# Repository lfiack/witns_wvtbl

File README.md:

# witns_wvtbl
Wavetable oscillator

## Make the project work
This project uses a submodule for the KiCAD library. To get it properly, use the `--recursive` option when cloning the repo :
```
git clone --recursive git@github.com:lfiack/witns_wvtbl.git
```

The firmware is developped with VSCode and the `stm32-for-vscode` plugin. There is now a plugin developped by ST, but I didn't take time to test it.

## Where to download wavetables ?
* [Free Serum Wavetables](https://www.antidoteaudio.com/free-serum-wavetables)
* [Adventurekid](https://www.adventurekid.se/akrt/waveforms/)

## TODO
* Add -12V Label

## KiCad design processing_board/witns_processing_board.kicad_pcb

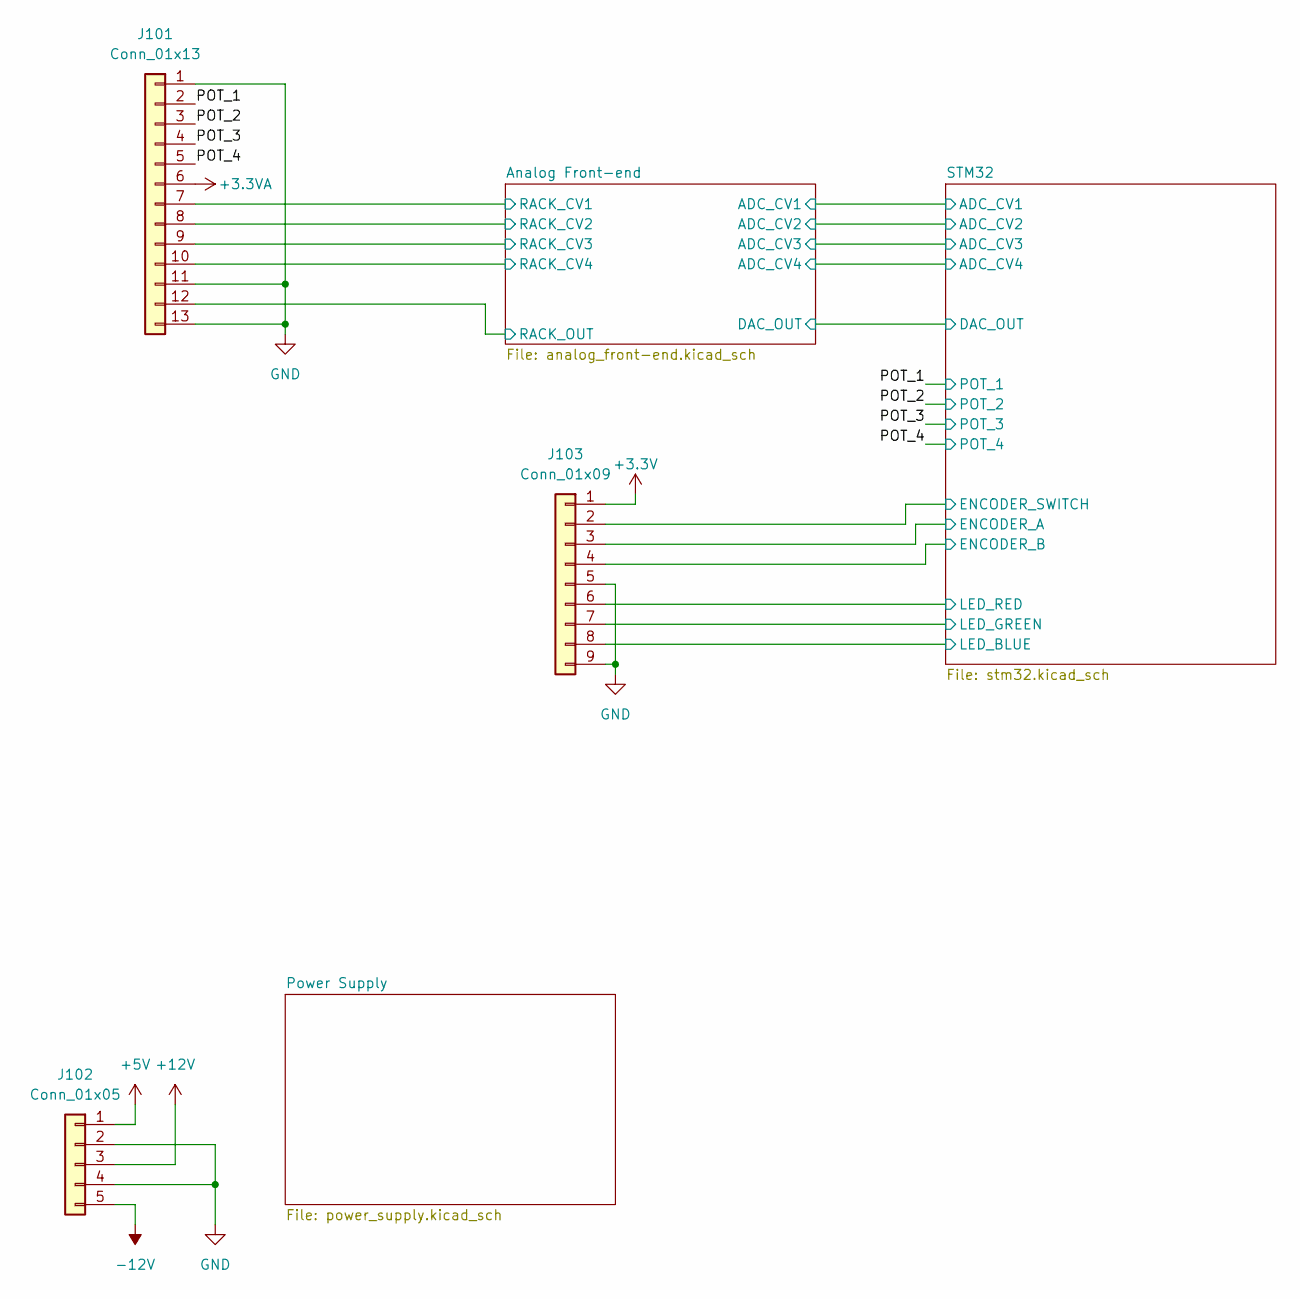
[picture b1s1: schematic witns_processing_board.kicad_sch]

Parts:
J101: Conn_01x13; PinHeader_1x13_P2.54mm_Vertical
J102: Conn_01x05; PinHeader_1x05_P2.54mm_Vertical
J103: Conn_01x09; PinHeader_1x09_P2.54mm_Vertical

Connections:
+3.3VA: J101.6; also elsewhere on the board
+3V3: J103.1; also elsewhere on the board
+5V: J102.1; also elsewhere on the board
+12V: J102.3; also elsewhere on the board
-12V: J102.5; also elsewhere on the board
/Analog Front-end/RACK_CV1: J101.7; also elsewhere on the board
/Analog Front-end/RACK_CV2: J101.8; also elsewhere on the board
/Analog Front-end/RACK_CV3: J101.9; also elsewhere on the board
/Analog Front-end/RACK_CV4: J101.10; also elsewhere on the board
/Analog Front-end/RACK_OUT: J101.12; also elsewhere on the board
/POT_1: J101.2; also elsewhere on the board
/POT_2: J101.3; also elsewhere on the board
/POT_3: J101.4; also elsewhere on the board
/POT_4: J101.5; also elsewhere on the board
/STM32/ENCODER_A: J103.3; also elsewhere on the board
/STM32/ENCODER_B: J103.4; also elsewhere on the board
/STM32/ENCODER_SWITCH: J103.2; also elsewhere on the board
/STM32/LED_BLUE: J103.8; also elsewhere on the board
/STM32/LED_GREEN: J103.7; also elsewhere on the board
/STM32/LED_RED: J103.6; also elsewhere on the board
GND: J101.1, J101.11, J101.13, J102.2, J102.4, J103.5, J103.9; also elsewhere on the board

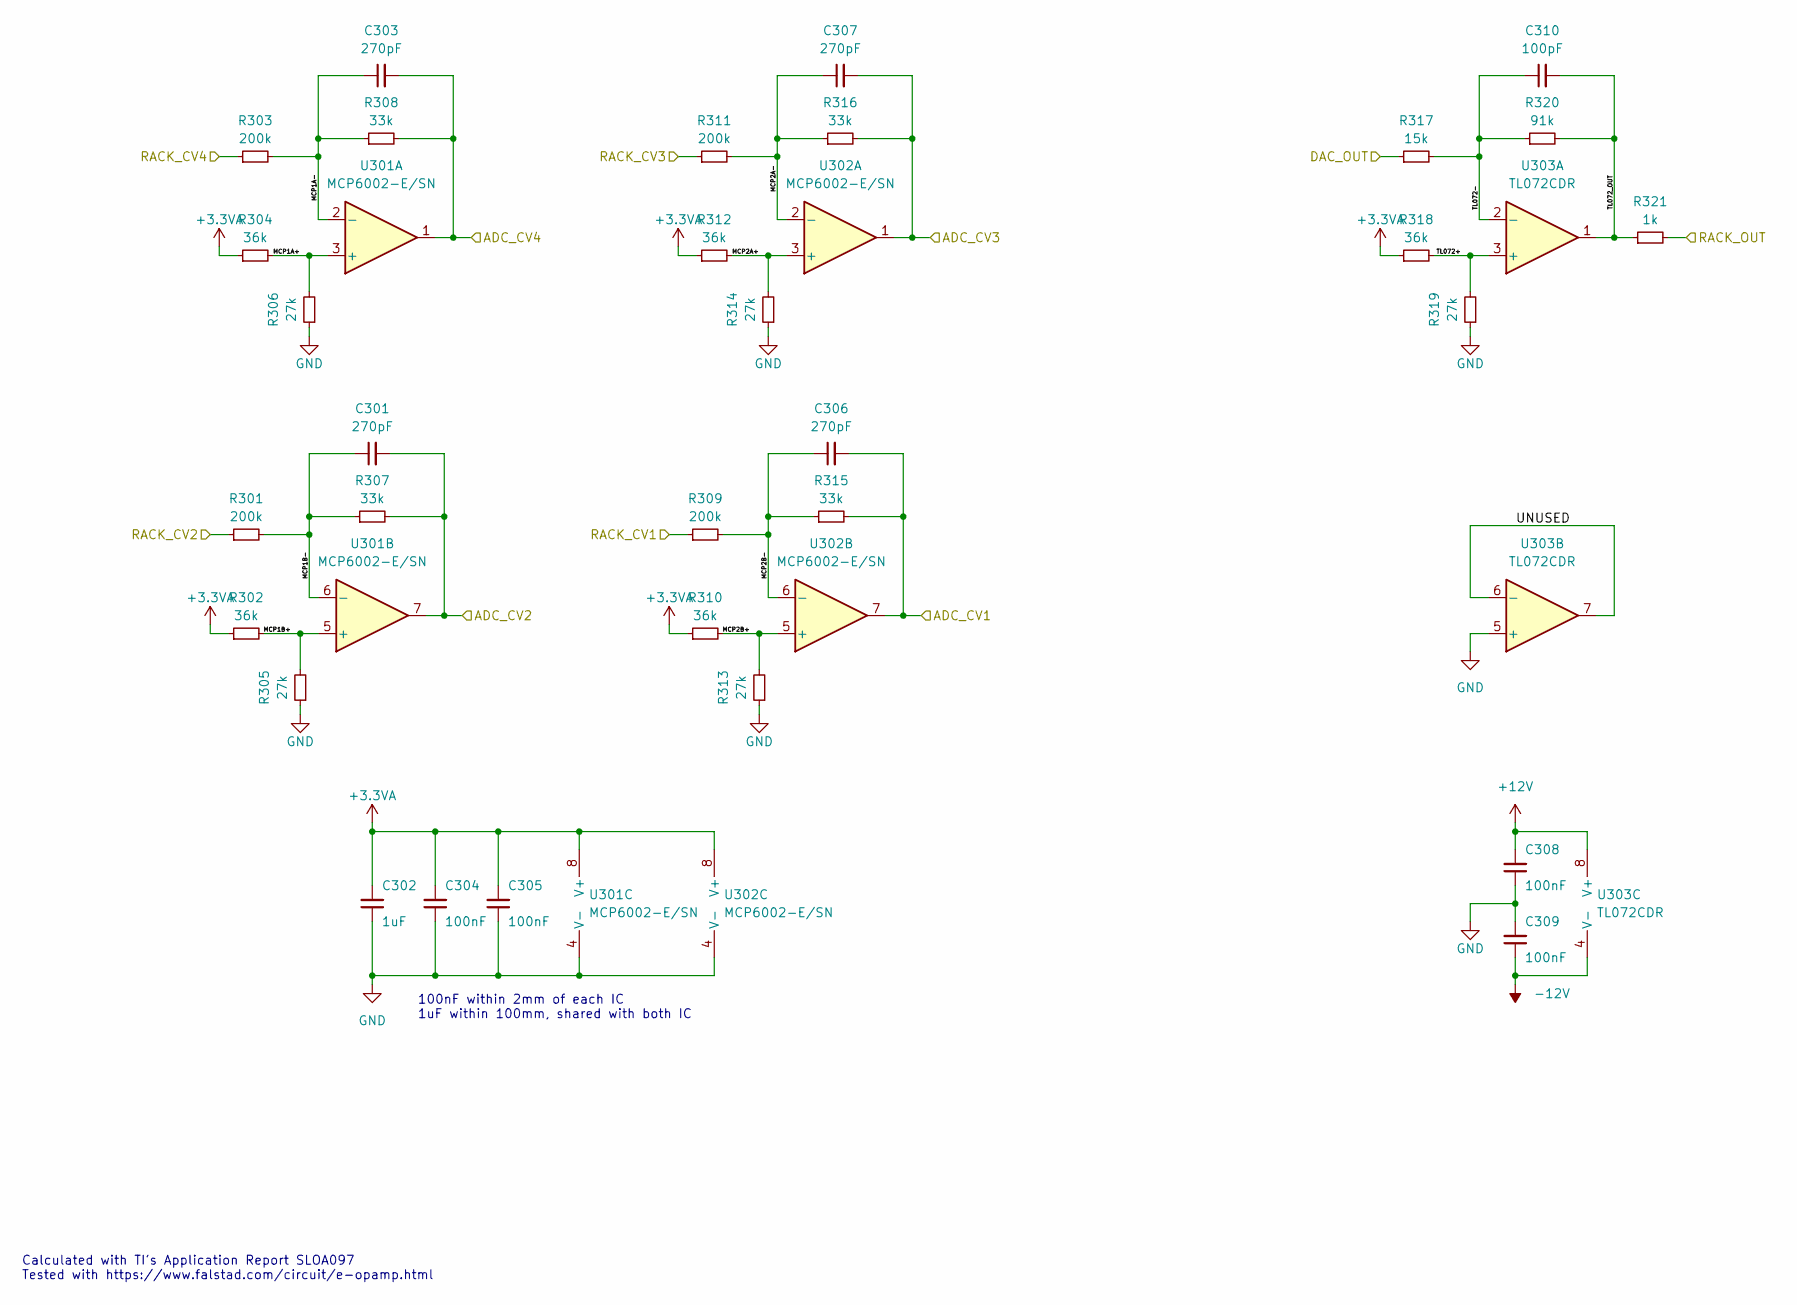
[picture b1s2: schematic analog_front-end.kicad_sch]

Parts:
C301, C303, C306, C307: 270pF; C_0603_1608Metric
C302: 1uF; C_0603_1608Metric
C304, C305, C308, C309: 100nF; C_0603_1608Metric
C310: 100pF; C_0603_1608Metric
R301, R303, R309, R311: 200k; R_0603_1608Metric
R302, R304, R310, R312, R318: 36k; R_0603_1608Metric
R305, R306, R313, R314, R319: 27k; R_0603_1608Metric
R307, R308, R315, R316: 33k; R_0603_1608Metric
R317: 15k; R_0603_1608Metric
R320: 91k; R_0603_1608Metric
R321: 1k; R_0603_1608Metric
U301, U302: MCP6002-E/SN; SOIC-8_3.9x4.9mm_P1.27mm
U303: TL072CDR; SOIC-8_3.9x4.9mm_P1.27mm

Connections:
+3.3VA: C302.2, C304.2, C305.2, R302.1, R304.1, R310.1, R312.1, R318.1, U301.8 (V+), U302.8 (V+); also elsewhere on the board
+12V: C308.2, U303.8 (V+); also elsewhere on the board
-12V: C309.1, U303.4 (V-); also elsewhere on the board
/Analog Front-end/ADC_CV1: C306.2, R315.2, U302.7; also elsewhere on the board
/Analog Front-end/ADC_CV2: C301.2, R307.2, U301.7; also elsewhere on the board
/Analog Front-end/ADC_CV3: C307.2, R316.2, U302.1; also elsewhere on the board
/Analog Front-end/ADC_CV4: C303.2, R308.2, U301.1; also elsewhere on the board
/Analog Front-end/DAC_OUT: R317.1; also elsewhere on the board
/Analog Front-end/MCP1A+: R304.2, R306.2, U301.3 (+)
/Analog Front-end/MCP1A-: C303.1, R303.2, R308.1, U301.2 (-)
/Analog Front-end/MCP1B+: R302.2, R305.2, U301.5 (+)
/Analog Front-end/MCP1B-: C301.1, R301.2, R307.1, U301.6 (-)
/Analog Front-end/MCP2A+: R312.2, R314.2, U302.3 (+)
/Analog Front-end/MCP2A-: C307.1, R311.2, R316.1, U302.2 (-)
/Analog Front-end/MCP2B+: R310.2, R313.2, U302.5 (+)
/Analog Front-end/MCP2B-: C306.1, R309.2, R315.1, U302.6 (-)
/Analog Front-end/RACK_CV1: R309.1; also elsewhere on the board
/Analog Front-end/RACK_CV2: R301.1; also elsewhere on the board
/Analog Front-end/RACK_CV3: R311.1; also elsewhere on the board
/Analog Front-end/RACK_CV4: R303.1; also elsewhere on the board
/Analog Front-end/RACK_OUT: R321.2; also elsewhere on the board
/Analog Front-end/TL072+: R318.2, R319.2, U303.3 (+)
/Analog Front-end/TL072-: C310.1, R317.2, R320.1, U303.2 (-)
/Analog Front-end/TL072_OUT: C310.2, R320.2, R321.1, U303.1
/Analog Front-end/UNUSED: U303.6 (-), U303.7
GND: C302.1, C304.1, C305.1, C308.1, C309.2, R305.1, R306.1, R313.1, R314.1, R319.1, U301.4 (V-), U302.4 (V-), U303.5 (+); also elsewhere on the board

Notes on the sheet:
100nF within 2mm of each IC 1uF within 100mm, shared with both IC
Calculated with TI's Application Report SLOA097 Tested with https://www.falstad.com/circuit/e-opamp.html

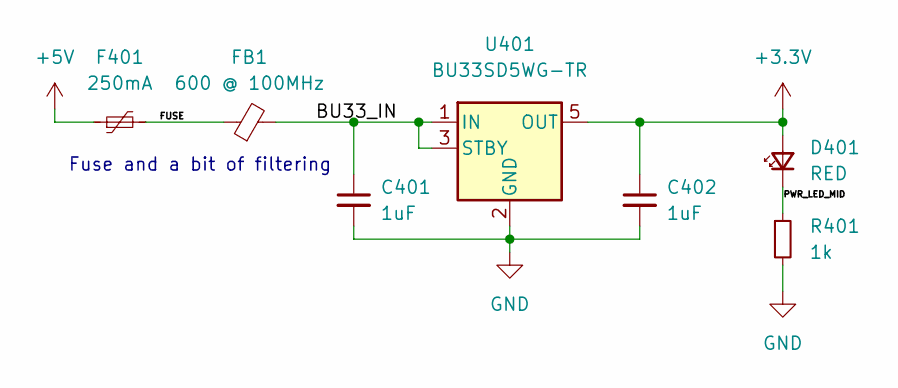
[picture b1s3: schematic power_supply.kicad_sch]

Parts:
C401, C402: 1uF; C_0603_1608Metric_Pad1.08x0.95mm_HandSolder
D401: RED; LED_0603_1608Metric_Pad1.05x0.95mm_HandSolder
F401: 250mA; Fuse_1206_3216Metric_Pad1.42x1.75mm_HandSolder; Farnell 2834880
FB1: 600 @ 100MHz; L_0805_2012Metric_Pad1.15x1.40mm_HandSolder; Farnell 2292460
R401: 1k; R_0603_1608Metric_Pad0.98x0.95mm_HandSolder
U401: BU33SD5WG-TR; SOT-23-5

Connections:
+3V3: C402.1, D401.2 (A), U401.5 (OUT); also elsewhere on the board
+5V: F401.1; also elsewhere on the board
/Power Supply/BU33_IN: C401.1, FB1.2, U401.1 (IN), U401.3 (STBY)
/Power Supply/FUSE: F401.2, FB1.1
/Power Supply/PWR_LED_MID: D401.1 (K), R401.1
GND: C401.2, C402.2, R401.2, U401.2 (GND); also elsewhere on the board

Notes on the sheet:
Fuse and a bit of filtering

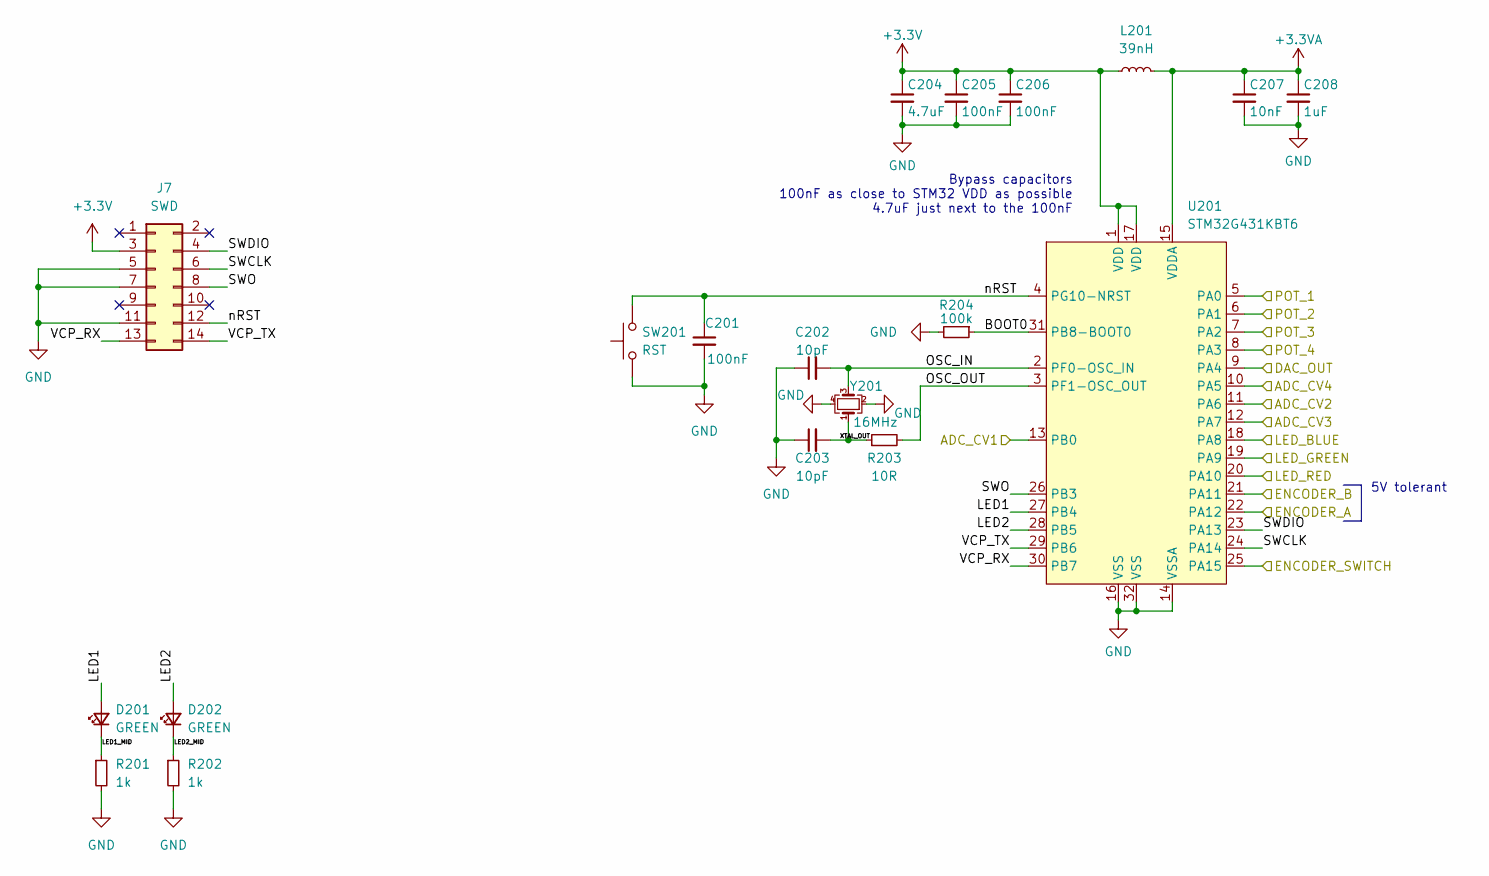
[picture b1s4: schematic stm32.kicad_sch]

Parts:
C201: 100nF; C_0603_1608Metric
C202, C203: 10pF; C_0603_1608Metric
C204: 4.7uF; C_0603_1608Metric_Pad1.08x0.95mm_HandSolder; Farnell 3013398
C205, C206: 100nF; C_0603_1608Metric_Pad1.08x0.95mm_HandSolder
C207: 10nF; C_0603_1608Metric_Pad1.08x0.95mm_HandSolder
C208: 1uF; C_0603_1608Metric_Pad1.08x0.95mm_HandSolder; Farnell 3013398
D201, D202: GREEN; LED_0603_1608Metric
J7: Conn_02x07_Odd_Even; PinHeader_2x07_P1.27mm_Vertical_SMD; Farnell 3226055
L201: 39nH; L_0603_1608Metric
R201, R202: 1k; R_0603_1608Metric
R203: 10R; R_0603_1608Metric
R204: 100k; R_0603_1608Metric
SW201: RST; SW_SPST_B3U-1000P; Farnell 1333652
U201: STM32G431KBT6; LQFP-32_7x7mm_P0.8mm
Y201: 16MHz; Crystal_SMD_EuroQuartz_MT-4Pin_3.2x2.5mm; Farnell 2853935

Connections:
+3.3VA: C207.1, C208.1, L201.2, U201.15 (VDDA); also elsewhere on the board
+3V3: C204.1, C205.1, C206.1, J7.3, L201.1, U201.1 (VDD), U201.17 (VDD); also elsewhere on the board
/Analog Front-end/ADC_CV1: U201.13 (PB0); also elsewhere on the board
/Analog Front-end/ADC_CV2: U201.11 (PA6); also elsewhere on the board
/Analog Front-end/ADC_CV3: U201.12 (PA7); also elsewhere on the board
/Analog Front-end/ADC_CV4: U201.10 (PA5); also elsewhere on the board
/Analog Front-end/DAC_OUT: U201.9 (PA4); also elsewhere on the board
/POT_1: U201.5 (PA0); also elsewhere on the board
/POT_2: U201.6 (PA1); also elsewhere on the board
/POT_3: U201.7 (PA2); also elsewhere on the board
/POT_4: U201.8 (PA3); also elsewhere on the board
/STM32/BOOT0: R204.1, U201.31 (PB8-BOOT0)
/STM32/ENCODER_A: U201.22 (PA12); also elsewhere on the board
/STM32/ENCODER_B: U201.21 (PA11); also elsewhere on the board
/STM32/ENCODER_SWITCH: U201.25 (PA15); also elsewhere on the board
/STM32/LED1: D201.2 (A), U201.27 (PB4)
/STM32/LED1_MID: D201.1 (K), R201.1
/STM32/LED2: D202.2 (A), U201.28 (PB5)
/STM32/LED2_MID: D202.1 (K), R202.1
/STM32/LED_BLUE: U201.18 (PA8); also elsewhere on the board
/STM32/LED_GREEN: U201.19 (PA9); also elsewhere on the board
/STM32/LED_RED: U201.20 (PA10); also elsewhere on the board
/STM32/OSC_IN: C202.2, U201.2 (PF0-OSC_IN), Y201.3
/STM32/OSC_OUT: R203.2, U201.3 (PF1-OSC_OUT)
/STM32/SWCLK: J7.6, U201.24 (PA14)
/STM32/SWDIO: J7.4, U201.23 (PA13)
/STM32/SWO: J7.8, U201.26 (PB3)
/STM32/VCP_RX: J7.13, U201.30 (PB7)
/STM32/VCP_TX: J7.14, U201.29 (PB6)
/STM32/XTAL_OUT: C203.2, R203.1, Y201.1
/STM32/nRST: C201.1, J7.12, SW201.2, U201.4 (PG10-NRST)
GND: C201.2, C202.1, C203.1, C204.2, C205.2, C206.2, C207.2, C208.2, J7.5, J7.7, J7.11, R201.2, R202.2, R204.2, SW201.1, U201.14 (VSSA), U201.16 (VSS), U201.32 (VSS), Y201.2, Y201.4; also elsewhere on the board

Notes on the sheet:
5V tolerant
Bypass capacitors 100nF as close to STM32 VDD as possible 4.7uF just next to the 100nF

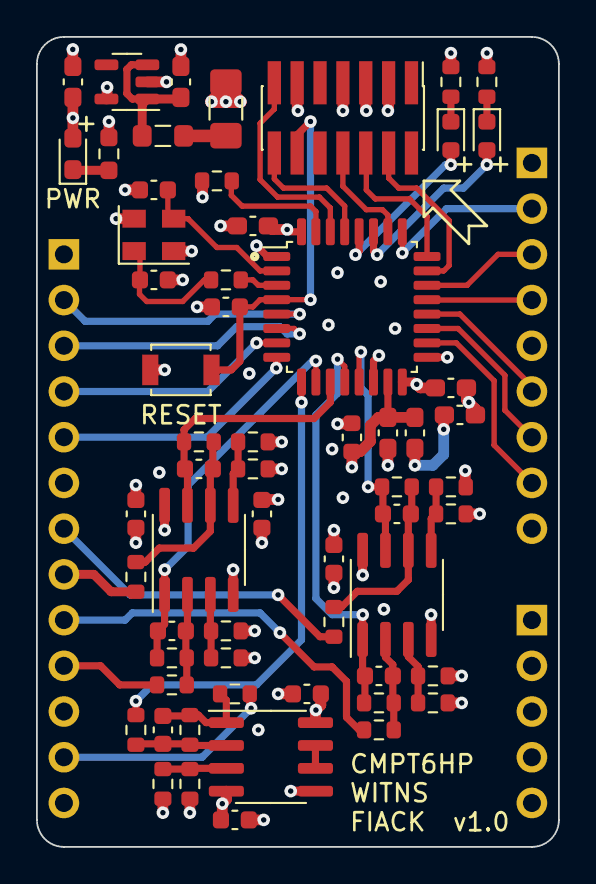
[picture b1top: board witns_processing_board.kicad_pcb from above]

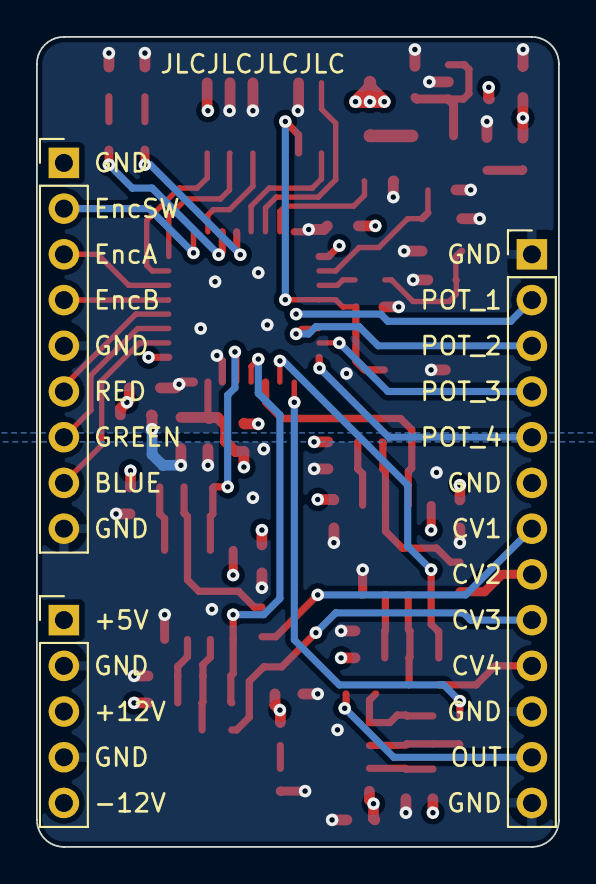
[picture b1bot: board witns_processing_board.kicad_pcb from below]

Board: 4 copper layers, 29.0 x 45.0 mm, 63 parts (3 on the bottom side), 55 nets.

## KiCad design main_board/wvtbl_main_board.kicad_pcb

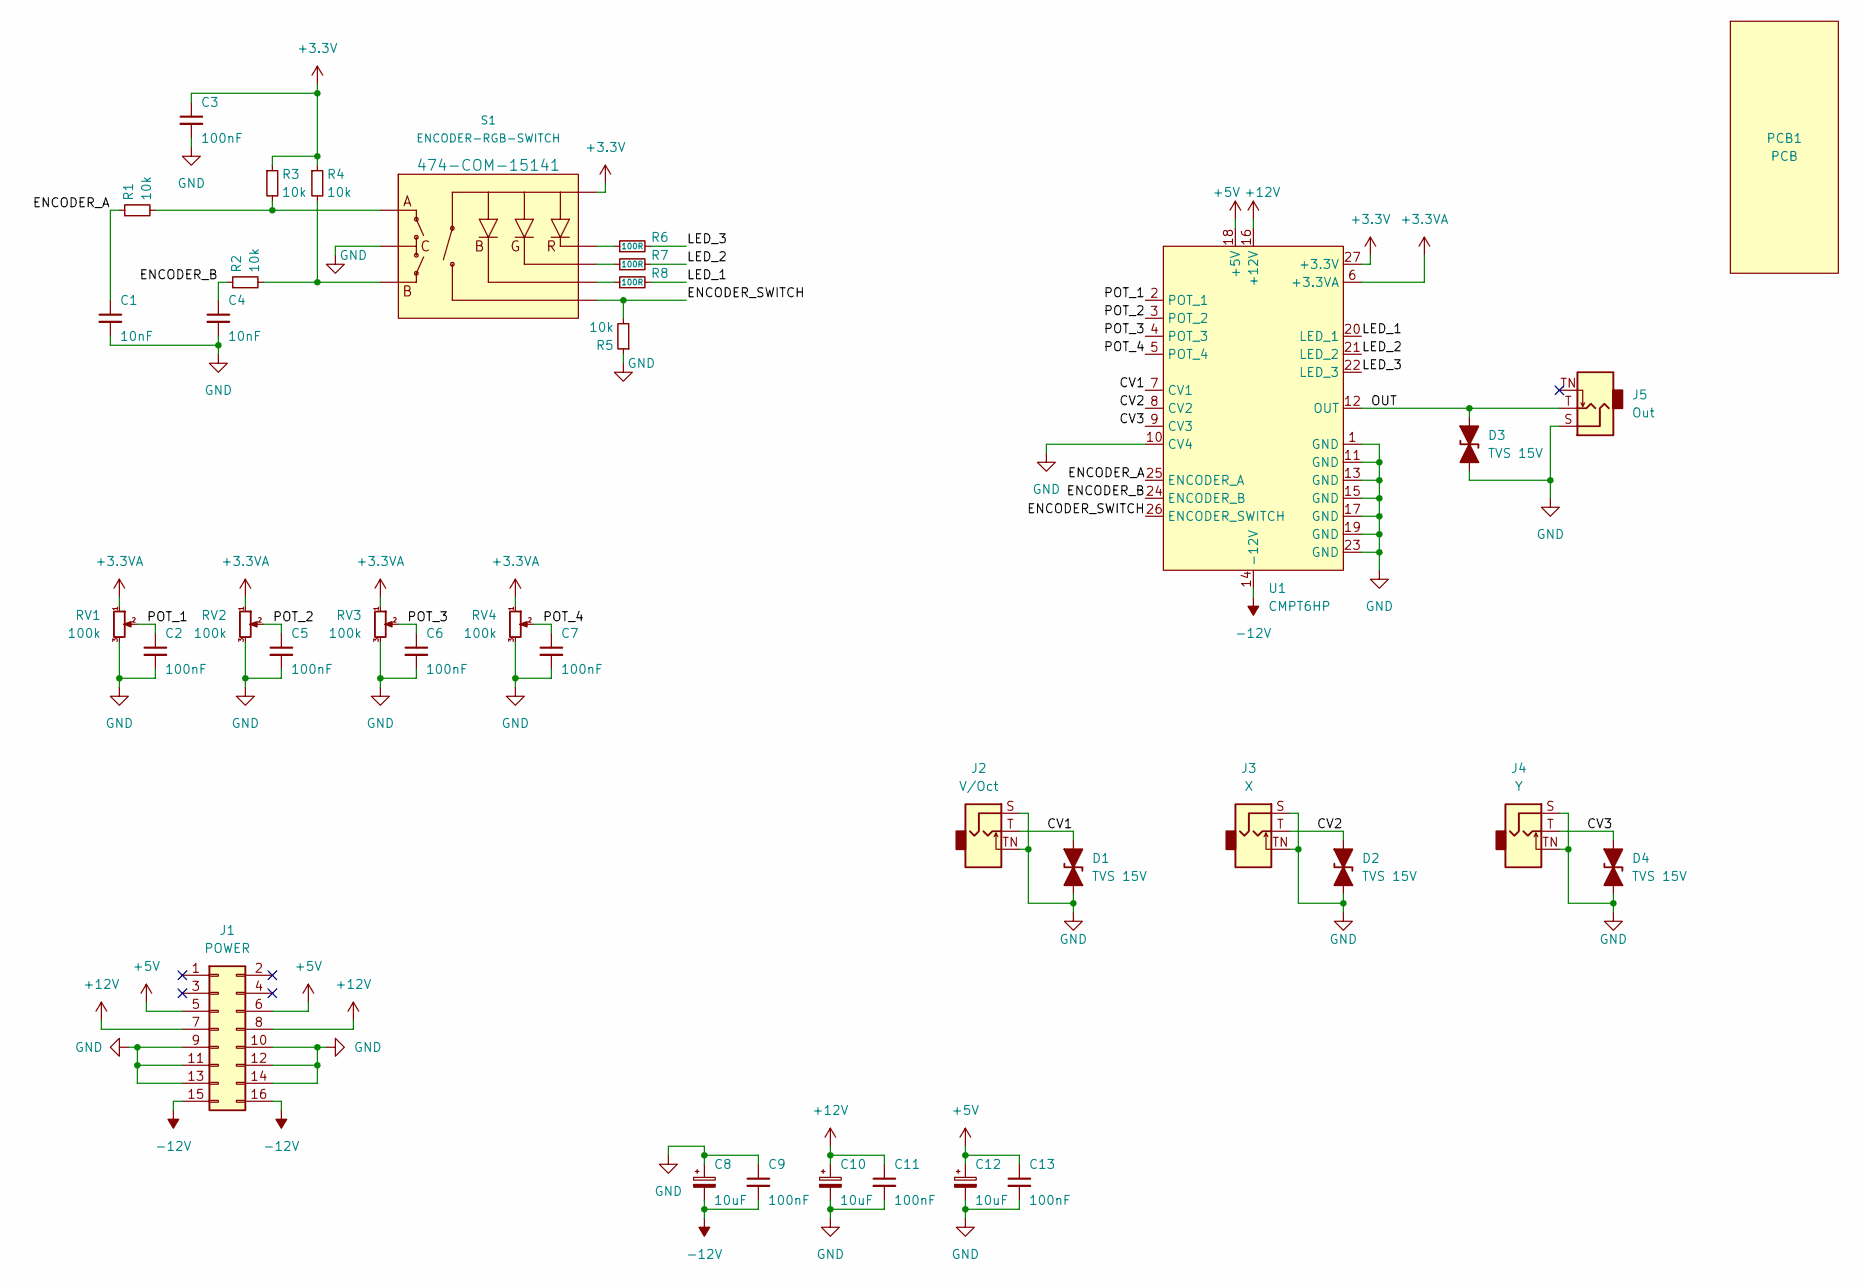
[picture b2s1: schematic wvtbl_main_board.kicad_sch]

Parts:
C1, C4: 10nF; C_0603_1608Metric
C2, C3, C5, C6, C7, C9, C11, C13: 100nF; C_0603_1608Metric
C8, C10, C12: 10uF; CP_Elec_4x5.4; Farnell 2611379
D1, D2, D3, D4: TVS 15V; D_SMA; Farnell 9802789
J1: POWER; PinHeader_2x08_P2.54mm_Vertical_SMD
J2: V/Oct; Jack_3.5mm_QingPu_WQP-PJ398SM_Vertical_CircularHoles
J3: X; Jack_3.5mm_QingPu_WQP-PJ398SM_Vertical_CircularHoles
J4: Y; Jack_3.5mm_QingPu_WQP-PJ398SM_Vertical_CircularHoles
J5: Out; Jack_3.5mm_QingPu_WQP-PJ398SM_Vertical_CircularHoles
PCB1: PCB; PCB_6HP
R1, R2, R3, R4, R5: 10k; R_0603_1608Metric
R6, R7, R8: 100R; R_0603_1608Metric
RV1, RV2, RV3, RV4: 100k; Potentiometer_Alpha_RD901F-40-00D_Single_Vertical
S1: ENCODER-RGB-SWITCH; ENCODER_LED_3; Mouser 474-COM-15141
U1: CMPT6HP

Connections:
+3.3V: C3.1, R3.1, R4.1, S1.5, U1.27 (+3.3V)
+3.3VA: RV1.1, RV2.1, RV3.1, RV4.1, U1.6 (+3.3VA)
+5V: C12.1, C13.1, J1.5, J1.6, U1.18 (+5V)
+12V: C10.1, C11.1, J1.7, J1.8, U1.16 (+12V)
-12V: C8.2, C9.2, J1.15, J1.16, U1.14 (-12V)
/CV1: D1.2 (A2), J2.T, U1.7 (CV1)
/CV2: D2.2 (A2), J3.T, U1.8 (CV2)
/CV3: D4.2 (A2), J4.T, U1.9 (CV3)
/ENCODER_A: C1.1, R1.1, U1.25 (ENCODER_A)
/ENCODER_B: C4.1, R2.1, U1.24 (ENCODER_B)
/ENCODER_SWITCH: R5.2, S1.3, U1.26 (ENCODER_SWITCH)
/LED_1: R8.2, U1.20 (LED_1)
/LED_2: R7.2, U1.21 (LED_2)
/LED_3: R6.2, U1.22 (LED_3)
/OUT: D3.2 (A2), J5.T, U1.12 (OUT)
/POT_1: C2.1, RV1.2, U1.2 (POT_1)
/POT_2: C5.1, RV2.2, U1.3 (POT_2)
/POT_3: C6.1, RV3.2, U1.4 (POT_3)
/POT_4: C7.1, RV4.2, U1.5 (POT_4)
GND: C1.2, C2.2, C3.2, C4.2, C5.2, C6.2, C7.2, C8.1, C9.1, C10.2, C11.2, C12.2, C13.2, D1.1 (A1), D2.1 (A1), D3.1 (A1), D4.1 (A1), J1.9, J1.10, J1.11, J1.12, J1.13, J1.14, J2.S, J2.TN, J3.S, J3.TN, J4.S, J4.TN, J5.S, R5.1, RV1.3, RV2.3, RV3.3, RV4.3, S1.C, U1.1 (GND), U1.10 (CV4), U1.11 (GND), U1.13 (GND), U1.15 (GND), U1.17 (GND), U1.19 (GND), U1.23 (GND)
unnamed: R1.2, R3.2, S1.A
unnamed: R2.2, R4.2, S1.B
unnamed: R6.1, S1.1
unnamed: R7.1, S1.2
unnamed: R8.1, S1.4

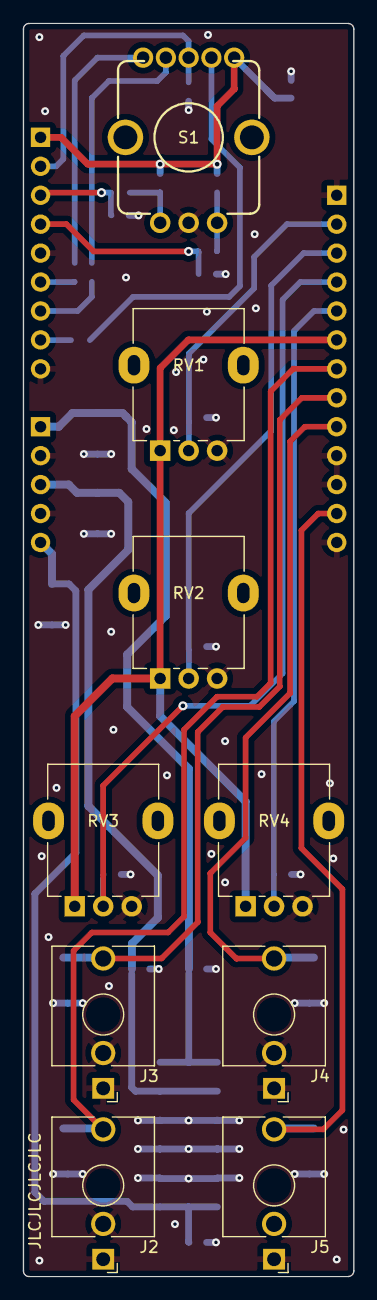
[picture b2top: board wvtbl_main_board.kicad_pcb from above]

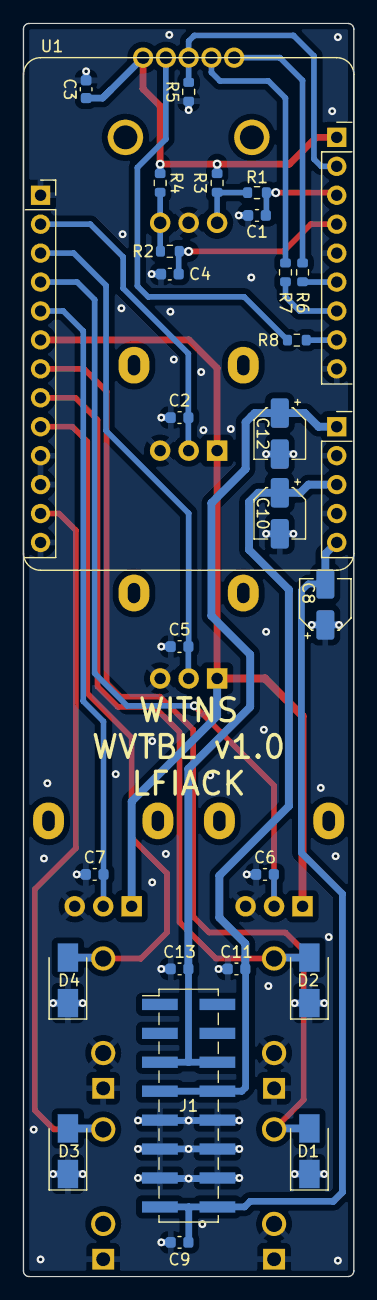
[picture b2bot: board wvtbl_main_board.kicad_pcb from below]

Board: 2 copper layers, 29.0 x 110.0 mm, 37 parts (27 on the bottom side), 25 nets.

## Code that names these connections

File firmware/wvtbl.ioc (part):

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Mcu.Name=STM32G431K(6-8-B)Tx
Mcu.Package=LQFP32
Mcu.UserName=STM32G431KBTx
PA0.GPIOParameters=GPIO_Label
PA0.GPIO_Label=POT_1
PA0.Mode=IN1-Single-Ended
PA0.Signal=ADC1_IN1
PA1.GPIOParameters=GPIO_Label
PA1.GPIO_Label=POT_2
PA1.Mode=IN2-Single-Ended
PA1.Signal=ADC1_IN2
PA10.GPIOParameters=GPIO_Label
PA10.GPIO_Label=LED_RED
PA10.Signal=S_TIM1_CH3
PA11.GPIOParameters=GPIO_Label
PA11.GPIO_Label=ENCODER_B
PA11.Signal=GPXTI11
PA12.GPIOParameters=GPIO_Label
PA12.GPIO_Label=ENCODER_A
PA12.Signal=GPXTI12
PA13.Mode=Trace_Asynchronous_SW
PA13.Signal=SYS_JTMS-SWDIO
PA14.Mode=Trace_Asynchronous_SW
PA14.Signal=SYS_JTCK-SWCLK
PA15.GPIOParameters=GPIO_Label
PA15.GPIO_Label=ENCODER_SWITCH
PA15.Signal=GPXTI15
PA2.GPIOParameters=GPIO_Label
PA2.GPIO_Label=POT_3
PA2.Mode=IN3-Single-Ended
PA2.Signal=ADC1_IN3
PA3.GPIOParameters=GPIO_Label
PA3.GPIO_Label=POT_4
PA3.Mode=IN4-Single-Ended
PA3.Signal=ADC1_IN4
PA4.GPIOParameters=GPIO_Label
PA4.GPIO_Label=DAC
PA4.Signal=SharedAnalog_PA4
PA5.GPIOParameters=GPIO_Label
PA5.GPIO_Label=CV1
PA5.Mode=IN13-Single-Ended
PA5.Signal=ADC2_IN13
PA6.GPIOParameters=GPIO_Label
PA6.GPIO_Label=CV2
PA6.Mode=IN3-Single-Ended
PA6.Signal=ADC2_IN3
PA7.GPIOParameters=GPIO_Label
PA7.GPIO_Label=CV3
PA7.Mode=IN4-Single-Ended
PA7.Signal=ADC2_IN4
PA8.GPIOParameters=GPIO_Label
PA8.GPIO_Label=LED_BLUE
PA8.Signal=S_TIM1_CH1
PA9.GPIOParameters=GPIO_Label
PA9.GPIO_Label=LED_GREEN
PA9.Signal=S_TIM1_CH2
PB0.GPIOParameters=GPIO_Label
PB0.GPIO_Label=CV4
PB0.Mode=IN15-Single-Ended
PB0.Signal=ADC1_IN15
PB3.Mode=Trace_Asynchronous_SW
PB3.Signal=SYS_JTDO-SWO
PB4.GPIOParameters=GPIO_Label
PB4.GPIO_Label=GPIO2
PB4.Signal=GPIO_Output
PB5.GPIOParameters=GPIO_Label
PB5.GPIO_Label=GPIO1
PB5.Signal=GPIO_Input
PB6.Mode=Asynchronous
PB6.Signal=USART1_TX
PB7.Mode=Asynchronous
PB7.Signal=USART1_RX
PF0-OSC_IN.Mode=HSE-External-Oscillator
PF0-OSC_IN.Signal=RCC_OSC_IN
PF1-OSC_OUT.Mode=HSE-External-Oscillator
PF1-OSC_OUT.Signal=RCC_OSC_OUT
RCC.HSE_VALUE=8000000
RCC.SYSCLKFreq_VALUE=16000000
board=custom

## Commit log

2023-01-25 library submodule
2023-01-25 schematics
2023-01-27 6HP Compute module
2023-01-29 Main board PCB
2023-01-29 fabrication files
2023-02-16 generated code for WVTBL firmware
2023-02-16 svd and vscode gitignore
2023-02-16 thinking about code organisation
2023-02-27 Waveform generation
2023-02-28 started ADC driver
2023-03-07 Test Encoder, LEDs, potentiometers
2023-03-07 notes on README
2023-03-08 tested analog front-end! +started writing a library
2023-03-08 encoder driver
2023-03-09 attempt of an analog driver
2023-03-14 led pwm driver
2023-03-17 Corrections on faceplate holes place and sizes
2023-03-17 DAC now uses DMA
2023-03-19 Ability to save stuff in the Flash
2023-03-21 kicad lib
2023-05-14 wavetable interpolation
2023-05-14 kicad_lib
2023-05-14 link to wavetables
2023-05-15 python script to generate wavetable
